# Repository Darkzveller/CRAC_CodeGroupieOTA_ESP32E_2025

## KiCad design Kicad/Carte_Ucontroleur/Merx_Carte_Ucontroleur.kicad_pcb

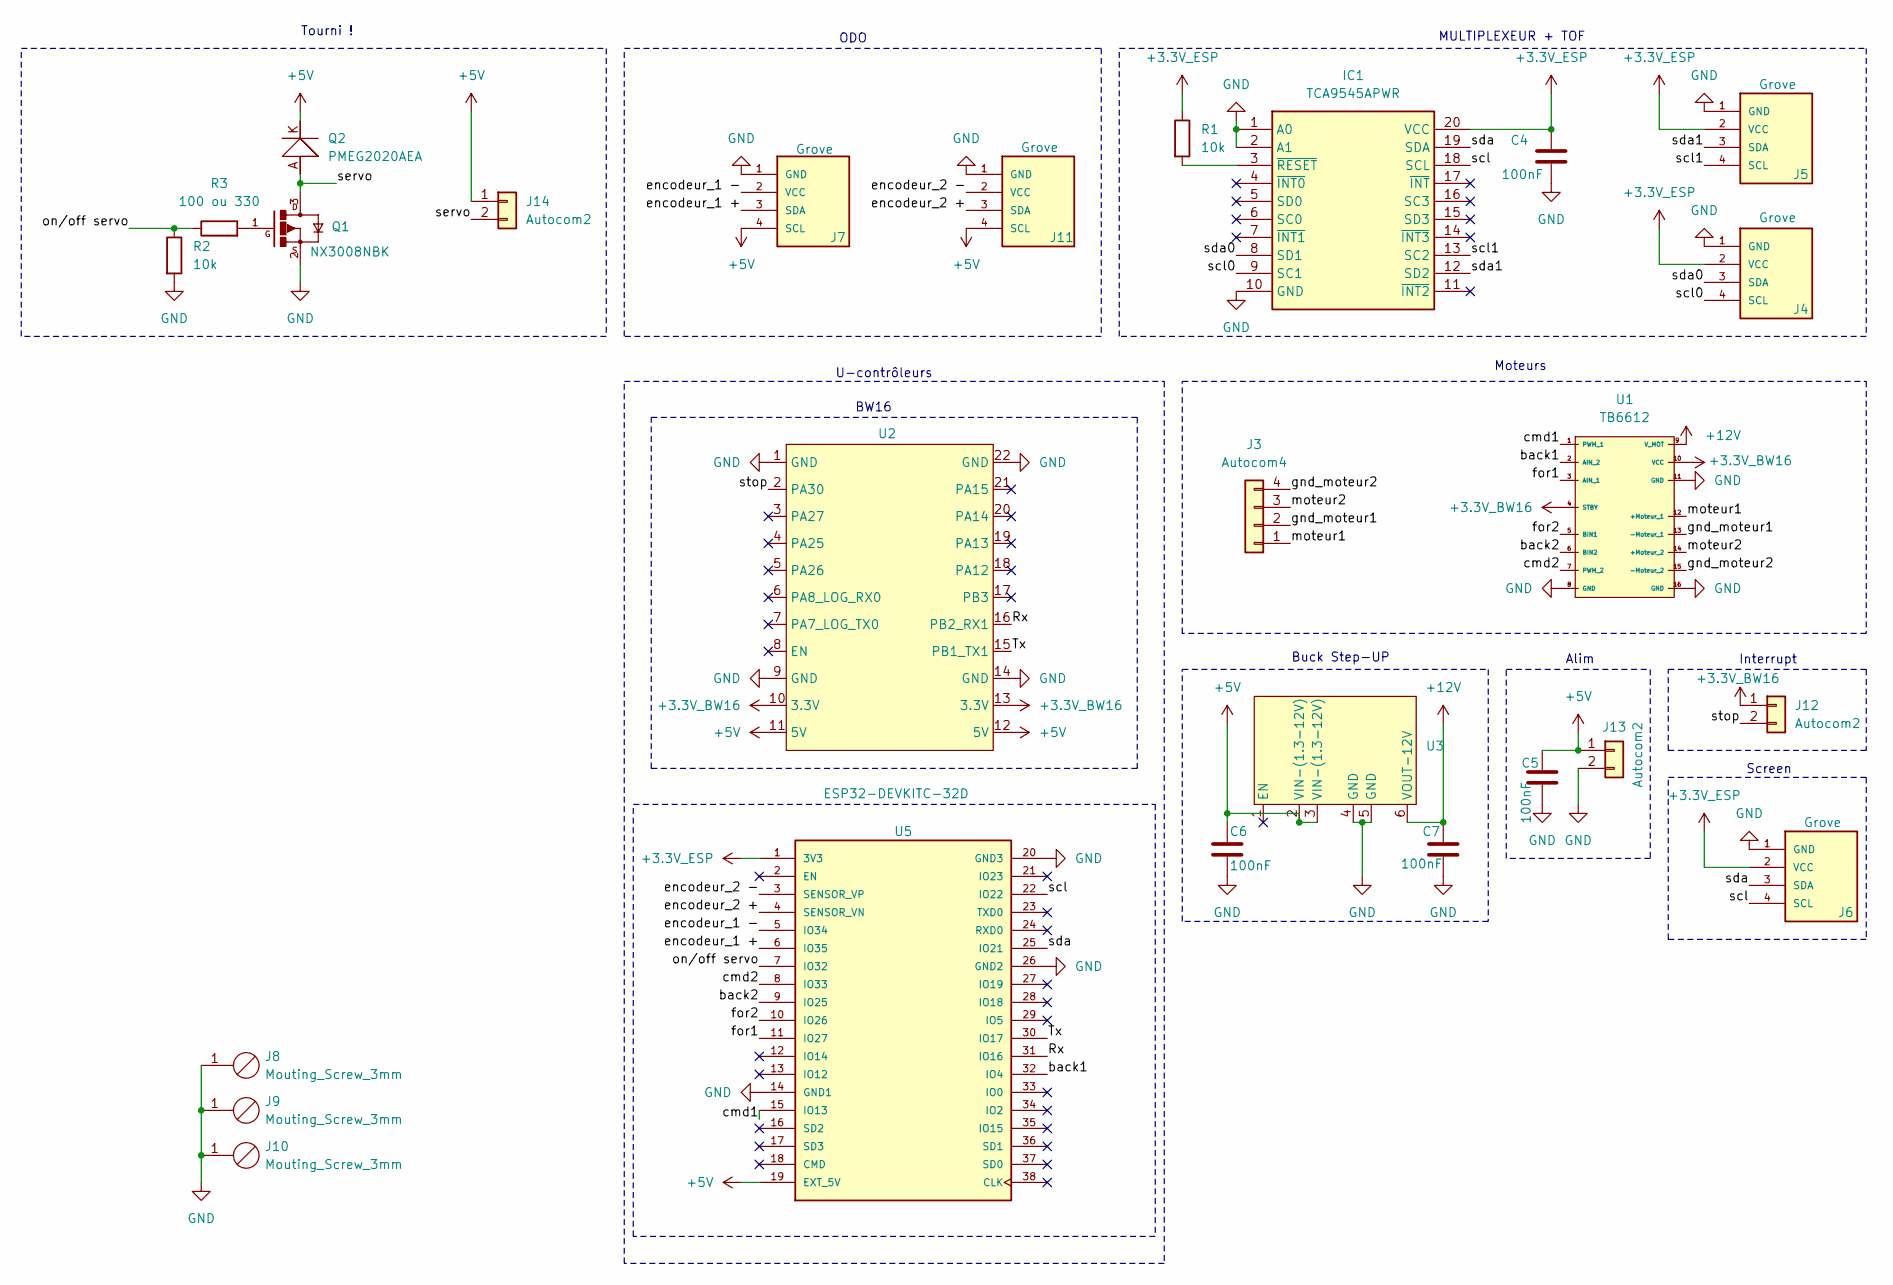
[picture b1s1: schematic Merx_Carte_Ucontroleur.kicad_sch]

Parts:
C4: 100nF; C_1206_3216Metric
C5, C6, C7: 100nF; C_Rect_L7.0mm_W2.5mm_P5.00mm
IC1: TCA9545APWR; SOP65P640X120-20N; Mouser Part Number 595-TCA9545APWR
J3: Autocom4
J4, J5, J6, J7, J11: Grove; SEEED_110990030
J8, J9, J10: Mouting_Screw_3mm; Mounting_Screw_3mm
J12, J13, J14: Autocom2
Q1: NX3008NBK; SOT23-3
Q2: PMEG2020AEA; DIO_BZX384-C30_115
R1, R2: 10k; R_1206_3216Metric
R3: 100 ou 330; R_1206_3216Metric
U1: TB6612; LibTB6612FNG
U2: BW16
U3: u3v40f12
U5: ESP32-DEVKITC-32D; MODULE_ESP32-DEVKITC-32D; PARTREV 4

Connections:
+3.3V_BW16: J12.1, U1.4 (STBY), U1.10 (VCC), U2.10 (3.3V), U2.13 (3.3V)
+3.3V_ESP: C4.1, IC1.20 (VCC), J4.2 (VCC), J5.2 (VCC), J6.2 (VCC), R1.1, U5.1 (3V3)
+5V: C5.1, C6.2, J7.4 (SCL), J11.4 (SCL), J13.1, J14.1, Q2.K, U2.11 (5V), U2.12 (5V), U3.2 (VIN-(1.3-12V)), U3.3 (VIN-(1.3-12V)), U5.19 (EXT_5V)
+12V: C7.2, U1.9 (V_MOT), U3.6 (VOUT-12V)
/Rx: U2.16 (PB2_RX1), U5.31 (IO16)
/Tx: U2.15 (PB1_TX1), U5.30 (IO17)
/back1: U1.2 (AIN_2), U5.32 (IO4)
/back2: U1.6 (BIN2), U5.9 (IO25)
/cmd1: U1.1 (PWM_1), U5.15 (IO13)
/cmd2: U1.7 (PWM_2), U5.8 (IO33)
/encodeur_1 +: J7.3 (SDA), U5.6 (IO35)
/encodeur_1 -: J7.2 (VCC), U5.5 (IO34)
/encodeur_2 +: J11.3 (SDA), U5.4 (SENSOR_VN)
/encodeur_2 -: J11.2 (VCC), U5.3 (SENSOR_VP)
/for1: U1.3 (AIN_1), U5.11 (IO27)
/for2: U1.5 (BIN1), U5.10 (IO26)
/gnd_moteur1: J3.2, U1.13 (-Moteur_1)
/gnd_moteur2: J3.4, U1.15 (-Moteur_2)
/moteur1: J3.1, U1.12 (+Moteur_1)
/moteur2: J3.3, U1.14 (+Moteur_2)
/on/off servo: R2.1, R3.1, U5.7 (IO32)
/scl: IC1.18 (SCL), J6.4 (SCL), U5.22 (IO22)
/scl0: IC1.9 (SC1), J4.4 (SCL)
/scl1: IC1.13 (SC2), J5.4 (SCL)
/sda: IC1.19 (SDA), J6.3 (SDA), U5.25 (IO21)
/sda0: IC1.8 (SD1), J4.3 (SDA)
/sda1: IC1.12 (SD2), J5.3 (SDA)
/servo: J14.2, Q1.3, Q2.A
/stop: J12.2, U2.2 (PA30)
GND: C4.2, C5.2, C6.1, C7.1, IC1.1 (A0), IC1.2 (A1), IC1.10 (GND), J4.1 (GND), J5.1 (GND), J6.1 (GND), J7.1 (GND), J8.1, J9.1, J10.1, J11.1 (GND), J13.2, Q1.2, R2.2, U1.8 (GND), U1.11 (GND), U1.16 (GND), U2.1 (GND), U2.9 (GND), U2.14 (GND), U2.22 (GND), U3.4 (GND), U3.5 (GND), U5.14 (GND1), U5.20 (GND3), U5.26 (GND2)
unnamed: IC1.3 (~RESET), R1.2
unnamed: Q1.1, R3.2

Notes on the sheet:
MULTIPLEXEUR + TOF
U-contrôleurs
Screen
Tourni !
Moteurs
BW16
Interrupt
Alim
Buck Step-UP
ODO

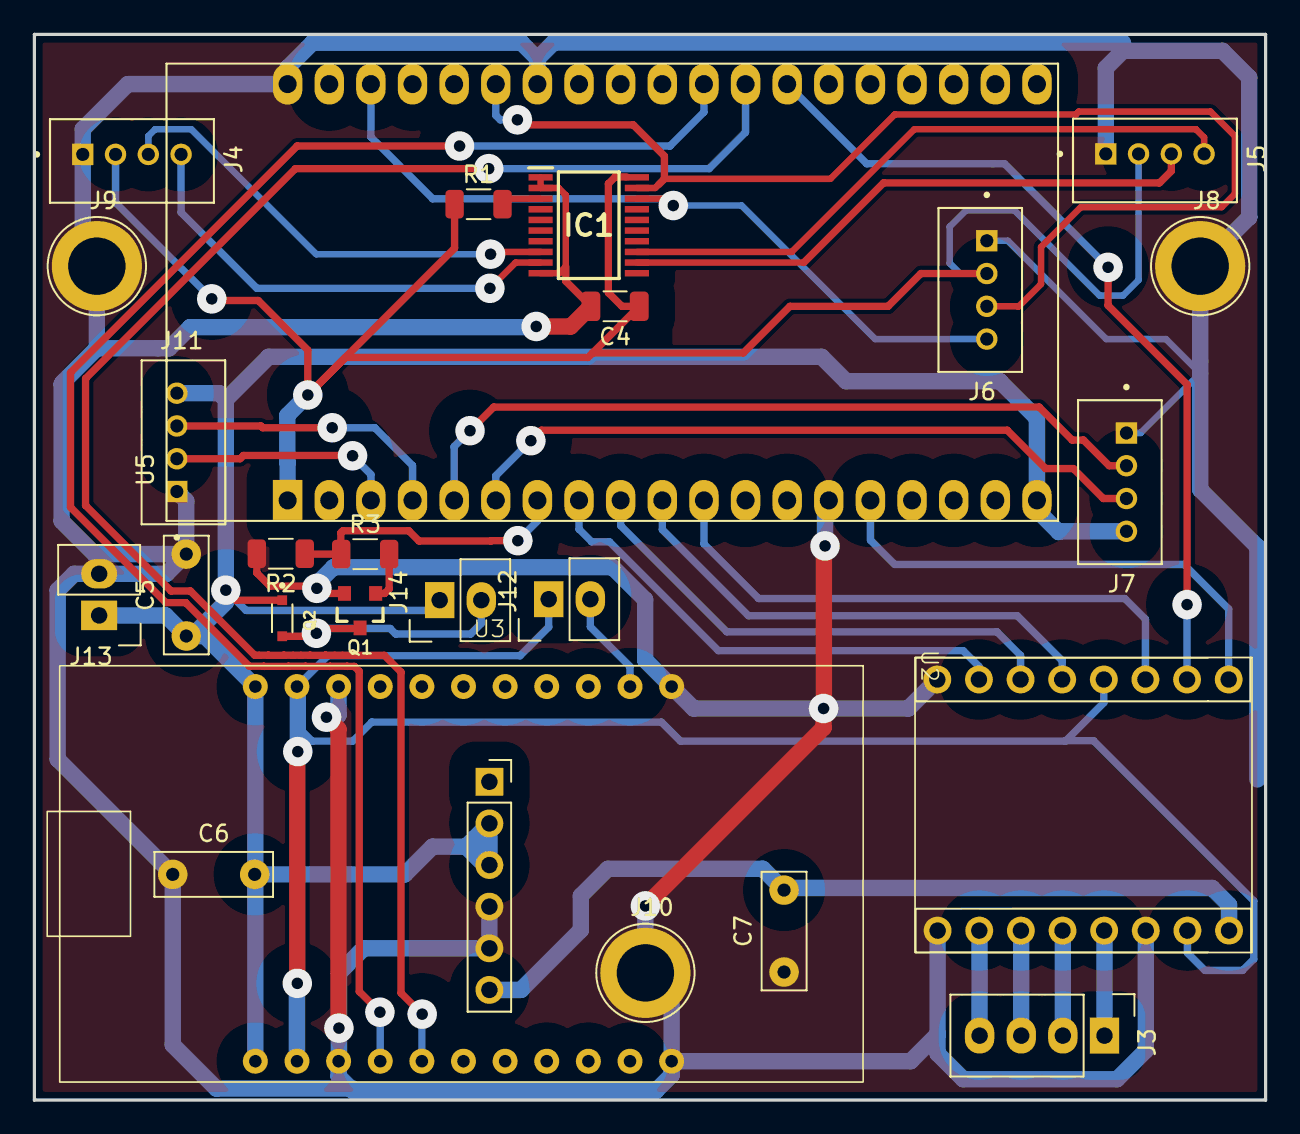
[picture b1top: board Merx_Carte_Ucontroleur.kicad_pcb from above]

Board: 2 copper layers, 75.1 x 65.0 mm, 26 parts (0 on the bottom side), 32 nets.

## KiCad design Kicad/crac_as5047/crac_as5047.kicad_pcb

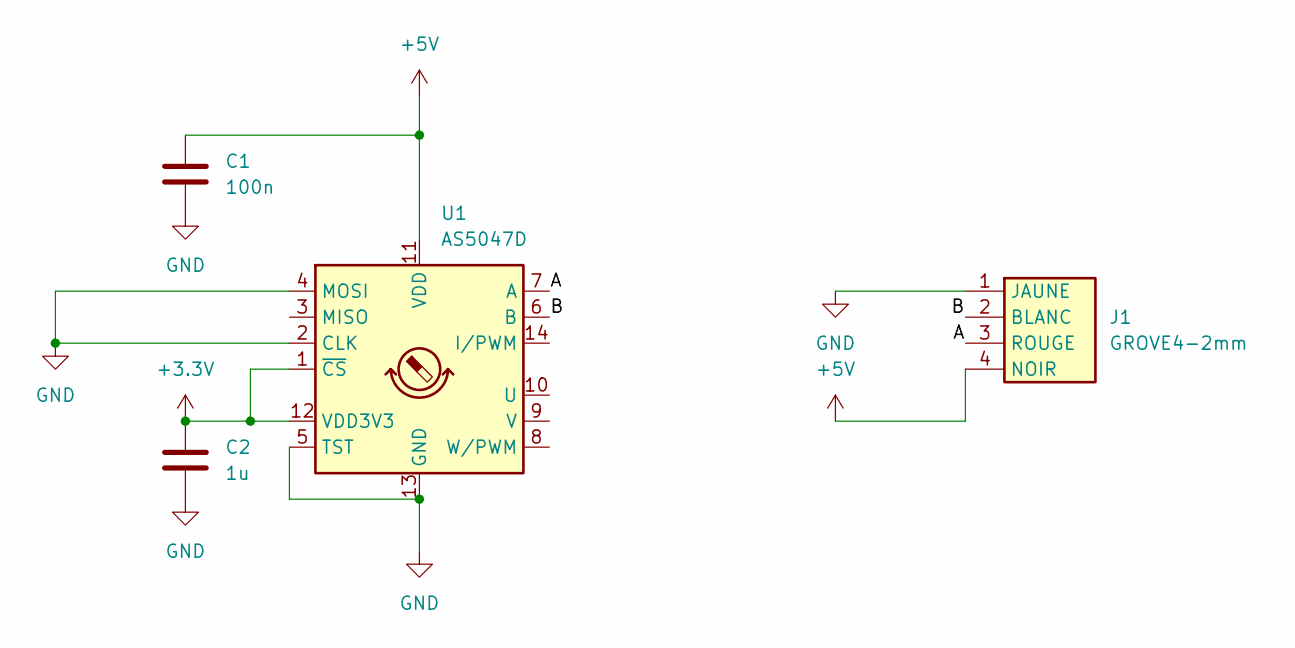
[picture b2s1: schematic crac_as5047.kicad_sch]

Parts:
C1: 100n; C_1206_3216Metric_Pad1.33x1.80mm_HandSolder
C2: 1u; C_1206_3216Metric_Pad1.33x1.80mm_HandSolder
J1: GROVE4-2mm; SEEED_110990037
U1: AS5047D; TSSOP-14_4.4x5mm_P0.65mm

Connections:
+3.3V: C2.1, U1.1 (~CS), U1.12 (VDD3V3)
+5V: C1.1, J1.4 (NOIR), U1.11 (VDD)
/A: J1.3 (ROUGE), U1.7 (A)
/B: J1.2 (BLANC), U1.6 (B)
GND: C1.2, C2.2, J1.1 (JAUNE), U1.2 (CLK), U1.4 (MOSI), U1.5 (TST), U1.13 (GND)

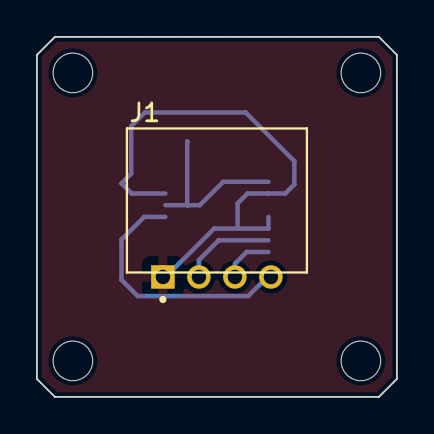
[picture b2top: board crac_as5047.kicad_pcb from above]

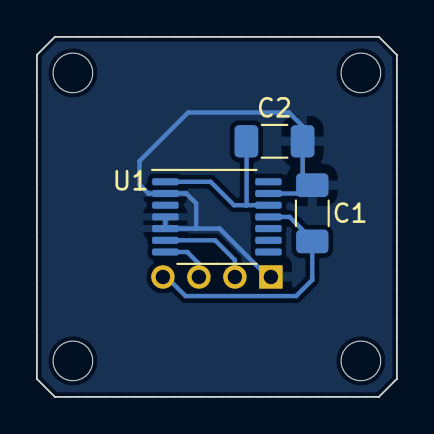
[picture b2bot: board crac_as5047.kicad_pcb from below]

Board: 2 copper layers, 20.0 x 20.0 mm, 4 parts (3 on the bottom side), 5 nets.

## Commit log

2025-03-31 Probleme-aide Git
2025-03-31 Modification des coefficient + création dossier Kicad avec les docs de la carte codeur et bibliotheque micromatch
2025-04-12 Ajout projet kicad 9 et non 8 faire attention
2025-04-19 Coeff de l'asservissement en position modifier + Réglage parametre physique et électronique+ Vitesse adéquat pour chaque fontion + UART 1 entre BW16 et Esp32 + simplification du polaire pour la group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
    Manque le recalage a faire qui est en cours de programmation.
2025-04-22 Mise en place du recalage + fonctionnalité sur l'ota + terminal wifi qui fonctionne très bien
2025-04-27 Polaire en marche arriere fonctionnelle et en avant
2025-04-27 Mise en commentaire de ligne de code Serial dans Mouvement concernant le polaire
2025-04-27 Retirag de f qui sont pas nécessaire dans le code
2025-05-03 Modification de x et y comme ca le robot voit mieux le terrain d'après Matthieu
2025-05-04 Modification des ID de ID CAN et changement de nom de ID can a ID UART
2025-05-08 Nouveau kIcad corrigé
2025-05-09 Bibliotheque du Tof inclus dans le projet et fonctionnelle, il faut faire la detection de si l'id du tof est déja préprogrammer ou non
2025-05-09 L'initialisation des TOF n'est plus bloquant, on observe les id des tof et s'ils sont déja initialiser on les begin juste et cela suffit amplement.
    PLus de delay d'attente, qui obligeait d'attendre que le tof s'initialise avant de le begin
2025-05-09 Ajout d'un petit commentaire dans if (id_tof_actuelle != 0x29)
2025-05-09 J'ai ranger les fichier dans le dossier tuto
2025-05-09 Evitement effectuer
2025-05-10 Mis en fonctionnement de l'écran lcd + retirer mutex qui en fin de compte n'était pas pertinent sans la tache i2c, mais j'ai créer une fonction init mutex, pour permettre de l'activer ou non au cas o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
2025-05-10 J'ai enlever les library properties de grove et VL5310X car sa fout la merde + ajout du moteur de la star + start and stop match
